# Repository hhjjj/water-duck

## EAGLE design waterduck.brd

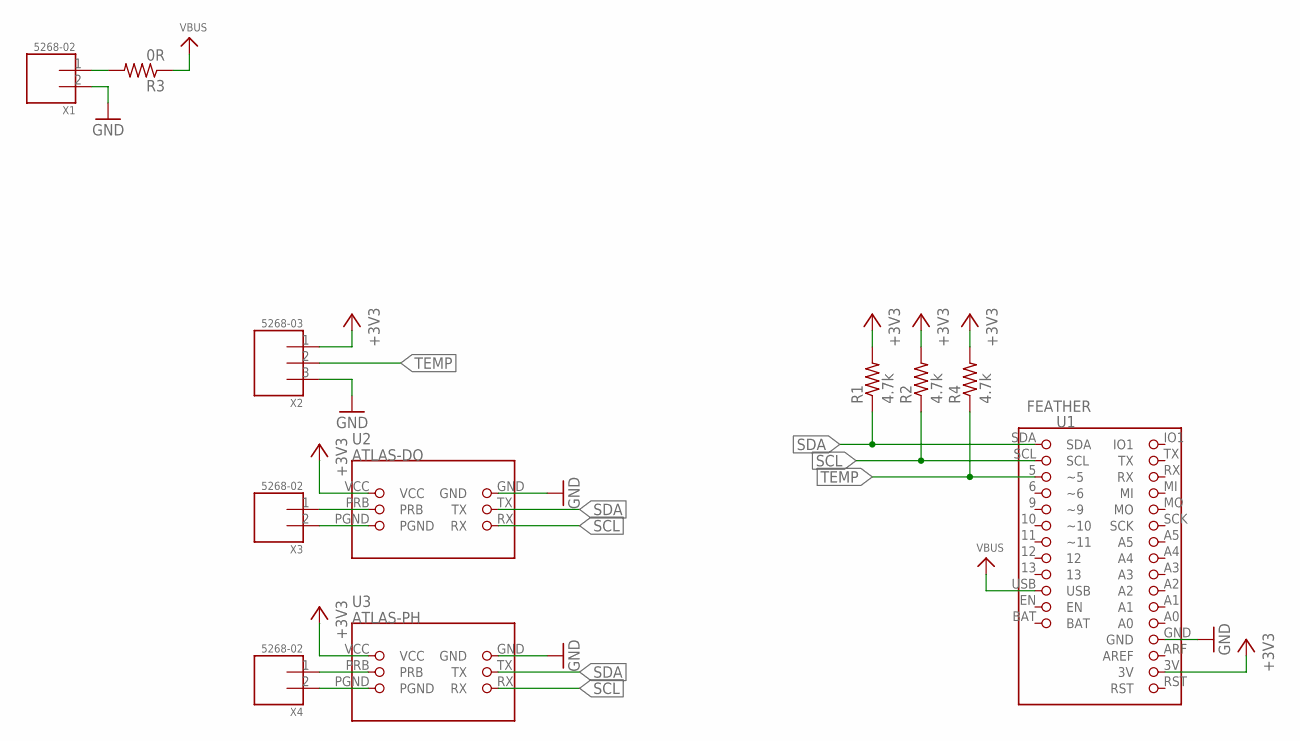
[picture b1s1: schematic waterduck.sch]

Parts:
R1, R2, R4: 4.7k; R0603(1608)
R3: 0R; R0603(1608)
U1: FEATHER
U2: ATLAS-DO; ATLAS
U3: ATLAS-PH; ATLAS
X1, X3, X4: 5268-02; 5628-02
X2: 5268-03

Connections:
+3V3: R1.2, R2.2, R4.2, U1.3V, U2.VCC, U3.VCC, X2.1
GND: U1.GND, U2.GND, U3.GND, X1.2, X2.3
unnamed: U2.PRB, X3.1
unnamed: U2.PGND, X3.2
unnamed: U3.PRB, X4.1
unnamed: U3.PGND, X4.2
unnamed: R3.2, X1.1
SCL: R2.1, U1.SCL, U2.RX, U3.RX
SDA: R1.1, U1.SDA, U2.TX, U3.TX
TEMP: R4.1, U1.5 (~5), X2.2
VBUS: R3.1, U1.USB

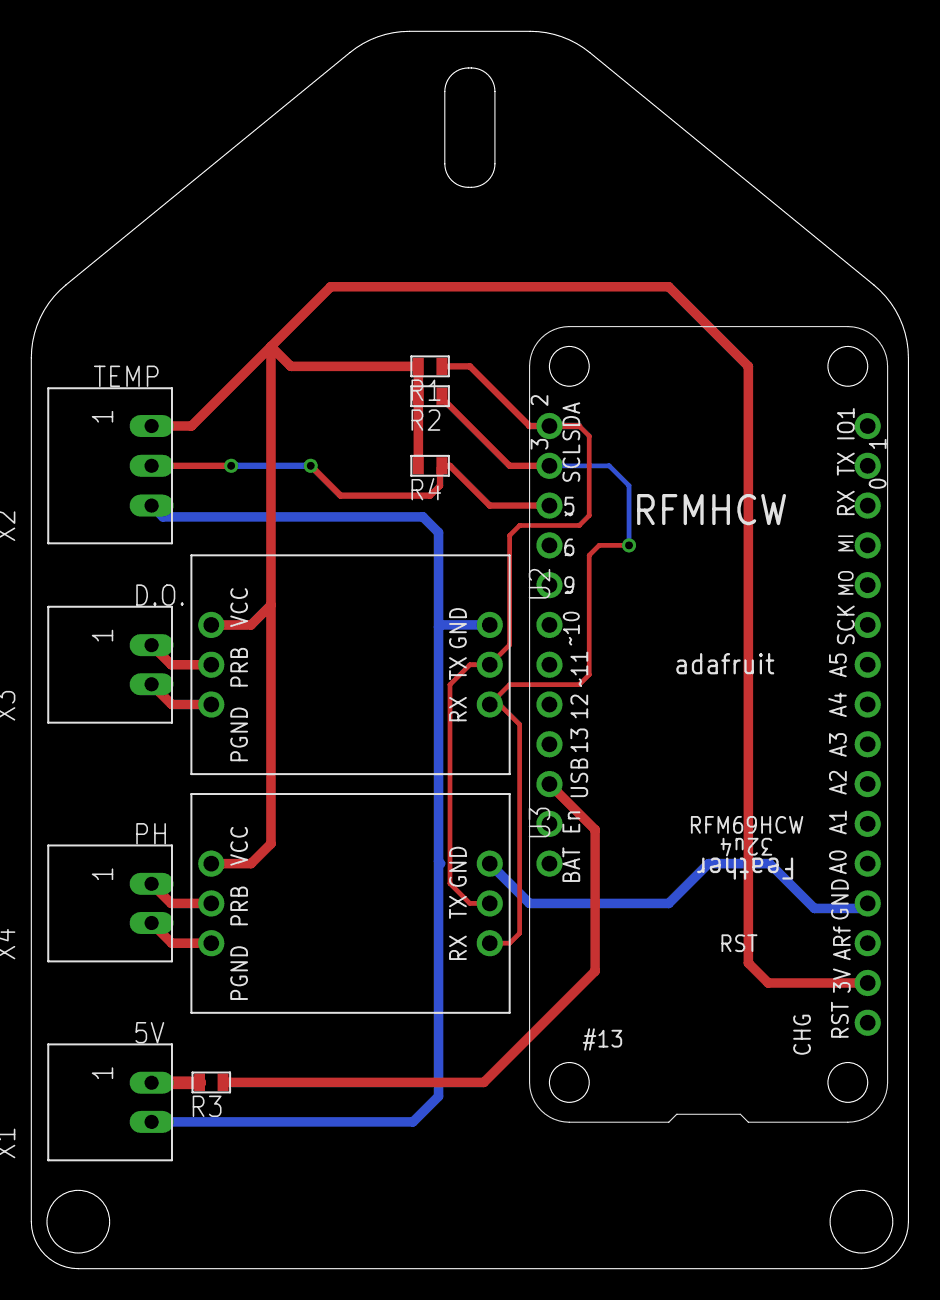
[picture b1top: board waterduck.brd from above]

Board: 2 copper layers, 56.0 x 79.0 mm, 11 parts (0 on the bottom side), 11 nets.

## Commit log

2017-01-10 :confetti_ball: Added .gitattributes
2017-01-10 first
2017-01-11 gerber

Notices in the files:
parts and their libraries:
microbuilder: This work is placed in the public domain, and may be freely used for commercial and non-commercial work with the following conditions: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
